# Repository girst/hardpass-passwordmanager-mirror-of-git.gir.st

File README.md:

# Hardpass Prototype, v.2
A Raspberry Pi Zero based WiFi Enabled Hardware Password Manager, now with a PCB.

## Currently Implemented:
 - OLED (demo)
 - USB Gadgets (full)
 - USB HID send keys progam

## TODO
- OLED: Menu program
- WiFi: compile & install driver
- Button Matrix (same program as OLED)

## Install ESP driver
If you want to use the ESP8266 on the SDIO pins of the Pi, download and install the driver from Andrew Litt.
```sh
# on the pi:
git clone https://github.com/al177/esp8089.git
make && sudo make install
```

## In this repository
This repository contains:
 * USB HID progam `scan` with examples in `./send_hid`
 * OLED menu system in `./oled`, using the `ArduiPi_OLED` driver from http://hallard.me
 * Patcher and installer for `pass` in `./pass`
 * KiCAD schematic and PCB layout in `./kicad`

## Setting up
To automatically load necessary kernel modules for the OLED on boot, run as root on the Pi:
```sh
echo "i2c-dev">>/etc/modules
echo "dwc2">>/etc/modules
```

A small systemd unit file is included; place it in `/etc/systemd/system/` and modify it, so it points to `init_usb.sh`, which you can also modify to your needs. 

## License
I hereby release my work under the GNU GPLv3 where applicable. The complete license text, if not included, can be read at `https://www.gnu.org/licenses/gpl-3.0.txt`. Where the GPLv3 isn't applicable, the work is released under the Creative Commons Attribution-ShareAlike 4.0 International. 
This repository also includes the ArduiPi_OLED library from [hallard](https://github.com/hallard); see [this website](http://hallard.me/adafruit-oled-display-driver-for-pi/) for details.
and the kicad-ESP8266 library from [jdunmire](https://github.com/jdunmire/kicad-ESP8266), which is released under the Creative Commons Attribution-ShareAlike 4.0 International License.

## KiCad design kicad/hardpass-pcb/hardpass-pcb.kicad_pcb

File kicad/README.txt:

hardpass PCB files
Copyright 2016 Tobias Girstmair, github.com/girst
Released as GPLv3, with exception to the libraries included. 

written on KiCad 4.0.3-4.0.6 on Ubuntu 16.04

Included are the following Libraries:
ESP-12 Footprint:
	https://github.com/jdunmire/kicad-ESP8266
	Copyright 2015 J.Dunmire
	Creative Commons Attribution-ShareAlike 4.0
adafruit-oled.pretty:
	extracted from adafruit's OLED breakout board. 
	https://github.com/adafruit/Adafruit-128x64-Monochrome-OLED-PCB
	Creative Commons Attribution, Share-Alike license
	(C) 2012 Adafruit Industries
RPi_Hat.pretty:
	https://github.com/xesscorp/RPi_Hat.pretty
	(C) 2015 XESS Corp.
	Mother Project (https://github.com/xesscorp/RPi_Hat_Template) MIT Licensed
hardpass.pretty:
	(C) 2015/2016 github.com/girst
	CC-BY-SA
	My own library, slightly modifying some default parts and the ESP-12E footprint from J.Dunmire. 

To the best of my knowledge, nothing but the above listed material in this folder is copyrighted. If your work has been included against the term of its license, please contact me  through the github issue tracker at http://github.com/girst/hardpass-passwordmanager/issues. 

Adafruit License Text (from https://github.com/adafruit/Adafruit-128x64-Monochrome-OLED-PCB/blob/master/README.txt): 
> This is the PCB for the Adafruit 128x64 I2C/SPI/Parallel OLED breakout board
> Format is EagleCAD schematic and board layout
> 
> For more details, check out the product page at
> 
> -----> http://www.adafruit.com/products/326
> 
> Adafruit invests time and resources providing this open source design, 
> please support Adafruit and open-source hardware by purchasing 
> products from Adafruit!
> 
> Designed by Adafruit Industries.  
> Creative Commons Attribution, Share-Alike license, check license.txt for more information
> All text above must be included in any redistribution

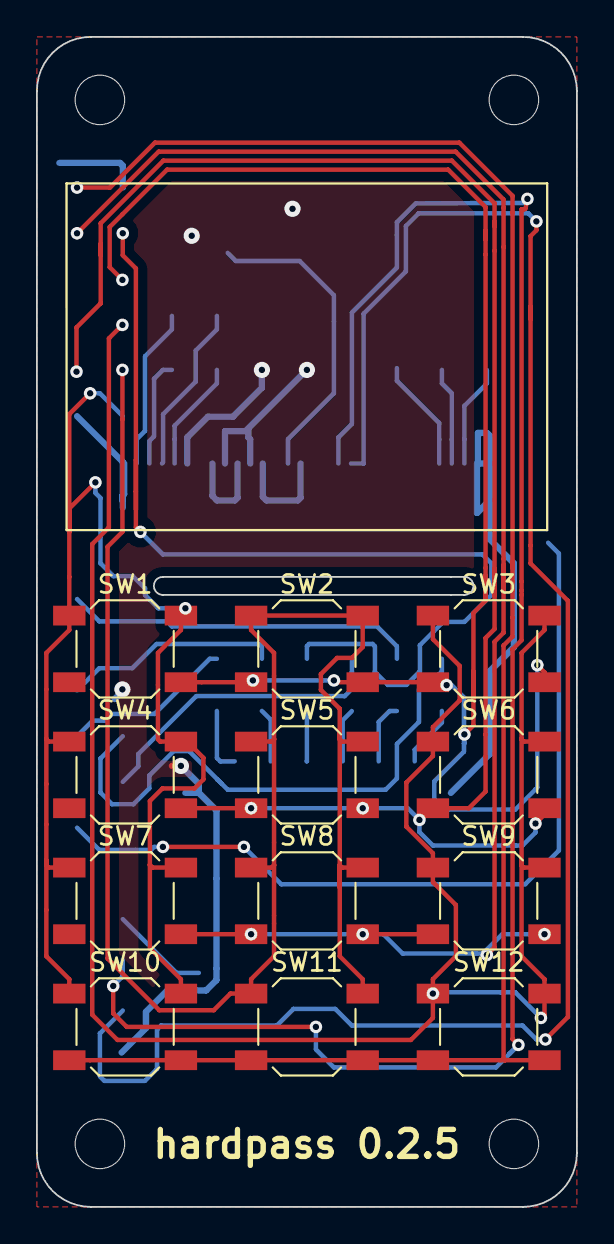
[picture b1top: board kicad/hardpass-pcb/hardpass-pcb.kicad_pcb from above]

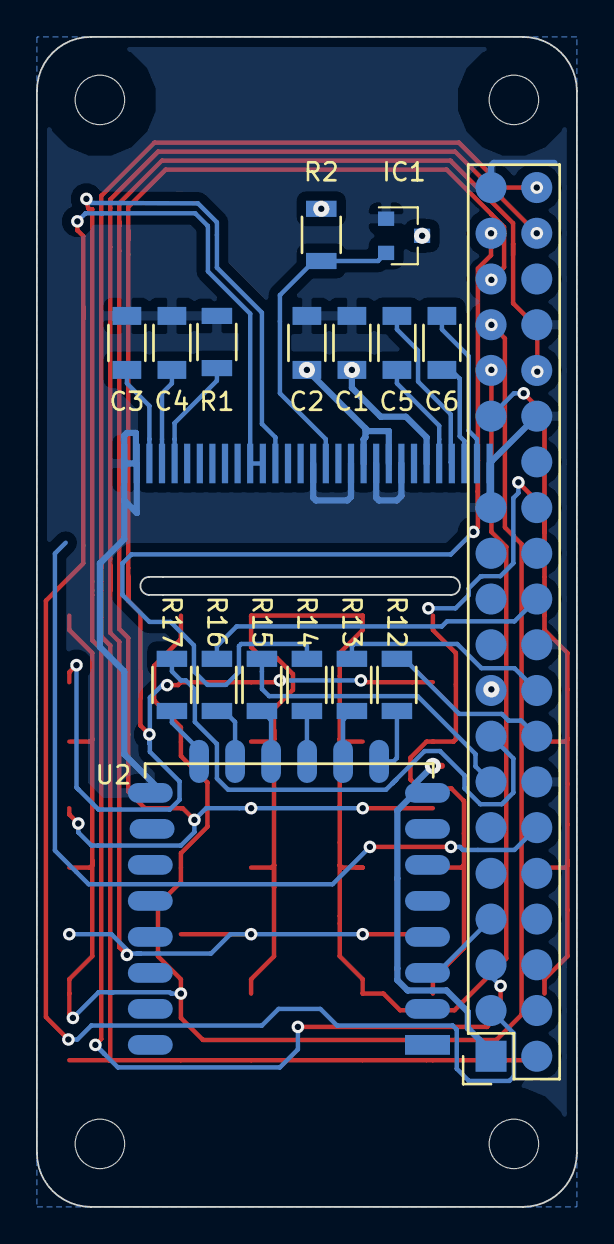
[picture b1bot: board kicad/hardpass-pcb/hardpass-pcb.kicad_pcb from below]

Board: 2 copper layers, 30.0 x 65.0 mm, 30 parts (17 on the bottom side), 32 nets.

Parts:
C1, C2, C4, C5, C6: 2.2µF; C_1206
C3: 10µF; C_1206
IC1: APX803; SOT-23
J1: Raspberry_Pi_2_3; Pin_Header_Mirrored-NoHoles_centered_2x20
P2: OLED_I2C; UG-2864HSWEG01_0.96IN_WRAPAROUND
R1: 390k; R_1206
R2: 10k; R_1206
R12, R13, R14, R15, R16, R17: 33; R_1206
SW1: 1; SW_SPST_SKQG
SW2: 2; SW_SPST_SKQG
SW3: 3; SW_SPST_SKQG
SW4: 4; SW_SPST_SKQG
SW5: 5; SW_SPST_SKQG
SW6: 6; SW_SPST_SKQG
SW7: 7; SW_SPST_SKQG
SW8: 8; SW_SPST_SKQG
SW9: 9; SW_SPST_SKQG
SW10: C/UP; SW_SPST_SKQG
SW11: 0/OK; SW_SPST_SKQG
SW12: OK/DN; SW_SPST_SKQG
U2: ESP-12E; ESP-12E_smd

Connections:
+3V3: C1.2, C2.2, IC1.3, J1.1, J1.17, P2.6, P2.9, P2.11, R2.1, U2.8
COL_1: J1.29, SW1.1, SW4.1, SW7.1, SW10.1
COL_2: J1.31, SW2.1, SW5.1, SW8.1, SW11.1
COL_3: J1.33, SW3.1, SW6.1, SW9.1, SW12.1
ESP_CHPD: J1.7, U2.3
ESP_CLK: J1.15, R17.2
GND: C1.1, C2.1, C3.2, C4.2, IC1.1, J1.14, J1.20, J1.25, J1.30, J1.34, J1.39, P2.1, P2.8, P2.10, P2.12, P2.15, P2.29, P2.30, R1.2, U2.15
unnamed: C3.1, P2.28
unnamed: C4.1, P2.27
unnamed: C5.1, P2.4
unnamed: C5.2, P2.5
unnamed: C6.1, P2.2
unnamed: C6.2, P2.3
unnamed: P2.26, R1.1
unnamed: R12.1, U2.9
unnamed: R13.1, U2.10
unnamed: R14.1, U2.11
unnamed: R15.1, U2.12
unnamed: R16.1, U2.13
unnamed: R17.1, U2.14
OLED_RST: IC1.2, P2.14, R2.2
OLED_SCL: J1.5, P2.18
OLED_SDA: J1.3, P2.19, P2.20
ROW_1: J1.35, SW1.2, SW2.2, SW3.2
ROW_2: J1.32, SW4.2, SW5.2, SW6.2
ROW_3: J1.38, SW7.2, SW8.2, SW9.2
ROW_4: J1.40, SW10.2, SW11.2, SW12.2
SD_CMD: J1.16, R12.2
SD_D0: J1.18, R13.2
SD_D1: J1.22, R16.2
SD_D2: J1.37, R14.2
SD_D3: J1.13, R15.2

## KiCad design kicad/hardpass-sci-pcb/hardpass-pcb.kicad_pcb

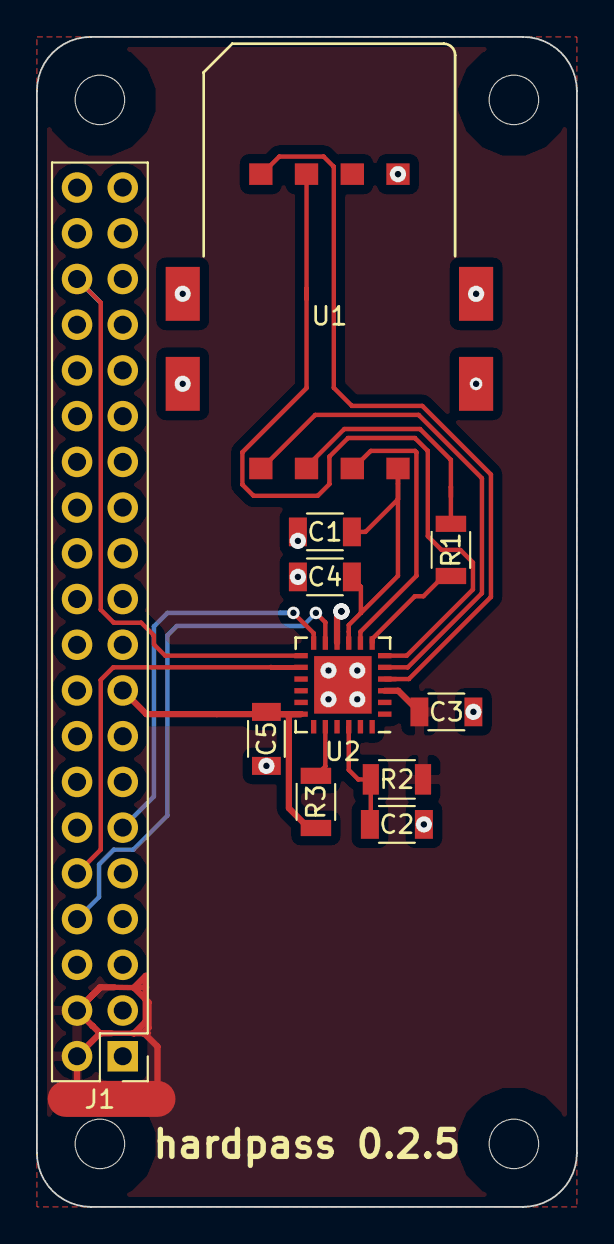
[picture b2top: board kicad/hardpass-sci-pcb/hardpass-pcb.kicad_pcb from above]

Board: 2 copper layers, 30.0 x 65.0 mm, 11 parts (0 on the bottom side), 16 nets.

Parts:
C1, C2: 100n; C_1206
C3, C4, C5: 1µ; C_1206
J1: Raspberry_Pi_2_3; Pin_Header_Straight_2x20_Pitch2.54mm_centered
R1: 43; R_1206
R2: 100K; R_1206
R3: 1M; R_1206
U1: ISO7816; CAF99-08153-S132
U2: SEC1210; QFN-24-1EP_5x5mm_Pitch0.65mm

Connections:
+3V3: C5.1, J1.1, J1.17, R3.1, U2.18
+5V: C3.1, J1.2, J1.4, R2.2, U2.3
CARD_CTS: J1.11, U2.12
CARD_RTS: J1.36, U2.13
CARD_RX: J1.8, U2.11
CARD_TX: J1.10, U2.14
GND: C1.2, C2.1, C3.2, C4.2, C5.2, J1.6, J1.9, J1.14, J1.20, J1.25, J1.30, J1.34, J1.39, U1.5, U2.10, U2.25
unnamed: C1.1, C4.1, U1.1, U2.9
unnamed: C2.2, R2.1, U2.22
unnamed: R3.2, U2.20
unnamed: R1.1, U2.7
unnamed: R1.2, U1.3
unnamed: U1.2, U2.8
unnamed: U1.4, U2.5
unnamed: U1.7, U2.6
unnamed: U1.8, U2.4

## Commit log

2016-08-20 Code import into new repository (long overdue)
2016-08-20 removed .git from subdirectories
2016-09-12 Actually use the device argument
    see https://github.com/girst/hardpass-sendHID/pull/2/files
2016-11-21 added reset circuit to oled
2016-11-21 removed spi labels from oled (won#t happen anyways)
2016-11-21 removed a few footprint labels for cleaner look
2017-01-07 re-done pcb for 30 pin oled
    pcb was completely redone, fixing header-misalignment (hopefully) and removing ugly silk screen from the front
2017-01-07 added logo
2017-01-18 add tda8029 footprint
2017-01-18 wired up tda8029
2017-01-18 moving stuff around the tda8029
    rotated schema back to normal
2017-01-18 added note to schema
    possible driver to use with the tda
2017-01-19 created footprint for sim slot
    will use a linkconn sim connector, available from aliexpress using the term 'samsung note n7000 i9000 9003 sim connector'
2017-01-19 added pin header for second board
2017-01-19 routed 2nd board
    not finished, but a start
2017-01-21 fixed bug (shdn_N), removed caps
    according to data sheet, shdn_n needs to be high to activate card (page43)
    2 bypass caps have been removed according to page 8 of AN00046
2017-01-21 board design work
2017-03-11 cleanup, but accidentally deleted smartcard-pcb
2017-03-11 Revert "cleanup, but accidentally deleted smartcard-pcb"
    This reverts commit a86da60cfe61b4d59f182c2c3fe14bc6cea5c2cc.
2017-03-11 change crystal to smd
    also added GND-netname to sim-mech-pads from within pcbnew. this will
    sadly automatically be reverted everytime you load the netlist, as i
    haven't bothered updating the footprint itself (then i'd have to add it
    in the schematic too, and that part is already pretty cluttered)
2017-03-11 added markers around potentially unnecessary capacitors
    keeping them in the schema until testing on physical board has been
    done.
2017-03-17 more file cleanup
    noticed some backup and drc files in there. oops
2017-03-17 update README to include adafruit license
    forgive me, for i have sinned by not including the adafruit license text
    for their awesome sd1306 footprint. the footprint was extracted from the
    eagle library with kicad's library editor.
2017-03-19 created 3d model for sim holder
    accuracy is questionable, but i call it good enough for a first try.
2017-03-19 idiot me can't double check pwd
2017-03-19 add 3d model to pcb
    used absolute filepath because kicad won't show it otherwise. bummer.
2017-03-19 cleanup tracks around xtal
2017-03-23 fixed multiple things, add gnu logo
    fixed:
    * mounting holes now non plated
    * fixed a few wires here and there
    * added a gnu/gpl logo for testing graphics
2017-06-10 reset circuit redesign WARN: multiple defined@once
2017-06-10 remove other non-ic reset methods
2017-07-22 reset circuit works; cleanup on it
2017-07-23 increase version number on pcb
2017-07-23 minimal cleanup on pcb
2017-08-25 fix missing trace on hardpass-scm
    also removes a small not-connected-to-anything trace under the oled.
2017-08-30 PCB cleanup silkscreen, fab-layer
    on the fabrication layer all the values of the small components like
    resistors and capactiors are now inside the footprints for easier
    referencing.
    the silk screen markings have been cleaned up as well, most notably
    moved them off the footprints on hardpass, and aligned them neatly on
    hardpass-sci, where some of the automatically placed ones were even on
2017-09-16 use relative paths for custom 3d models
    i tried to do this before, but pcbnew just moved up the directory tree until it hit root (using ../), then used the absolute path again.
    kicad.info forums suggested to use ${KIPRJMOD}, which works.
2017-09-16 add model for ssd1306
    i finally managed to convince joe su to relicense monitor_tinyscreen under a
    free license. his model has now been included in hardpass' kicad project, and
    he is credited inhardpass.3dshapes/README.md
2017-09-16 ssd1306: 3d model flatflex; correct thickness
    also includes blender model and wings-file (for coloring)
2018-01-28 switch smartcard chip to microchip SEC1210
2018-01-28 copy new sec1210 library into gitdir
2018-01-30 small fixes
    schematic: add either-or text to card-led
    pcb: connect c10 to card-pin1
2018-02-10 seperate hardpass and hardpass-sci kicad projects
2018-02-10 seperate hardpass-frontend from hardpass-sci, II
    (I) was sci
    (II) is frontend
    also general cleanup and version bump to 0.2.5
2018-02-10 redesign frontend with 5.2mm tact switches
    reason being, those are flat enough so they don't protrude above the
    oled. I'm thinking about putting a lasercut sheet of plexiglass as a
    protecting case in front
2018-02-10 use realistic colors for 5.2mm tact switches
    as it turns out, step files are plain text -- so search and replace can
    be used to modify colors reliably
    search for colors:
    grep COLOUR_RGB SKQGAF-realcolors.STEP|awk -F= '{print $2}'|sort|uniq -c
    replace them with
    sed -i "s/$OLDCOLOR/$NEWCOLOR/" SKQGAF-realcolors.STEP
2018-02-11 cleanup on the frontend-pcb
2018-02-11 cleanup frontend-pcb some more, shutdown-button-note
2018-02-11 more shutdown-button routing
2018-02-25 change sec1210 footprint to handsoldering
    should ease qfn soldering by hand due to the elongated pads. this also
    required moveing some traces out of the way on the pcb.
